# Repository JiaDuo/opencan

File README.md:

# opencan
linux系统下开源的can测试工具
基于linux驱动中slcan协议实现socketcan的通信  

## 硬件介绍  
硬件使用MicroUSB和PC主机通信，支持一路CAN 2.0B，最大波特率1Mbps
## 更新固件
使用stlink/jlink连接到J2引脚，CLK DIO GND  

linux系统下安装stlink-tools  
apt install stlink-tools  

下载固件到MCU中  
st-flash --reset write ./build/usb2can.bin 0x08000000  

## 使用
基于slcan/socketcan的软件都可以应用到当前设备，python-can、can-utils等     
* 安装can-utils  
apt install can-utils
* 建立socketcan设备  
slcand -o -s8 /dev/ttyACM0 can0   
ip link set up can0
* 收发报文
可以使用ifconfig查看can网络状态，使用can-utils中提供的软件来进行报文收发  
eg：  
candump can0  
cansniffer -c can0  
cansend can0 123#R3  

## 一些参考文档
[slcan]https://elinux.org/Bringing_CAN_interface_up  
[slcan-api]https://github.com/linux-can/can-misc/blob/master/docs/SLCAN-API.pdf

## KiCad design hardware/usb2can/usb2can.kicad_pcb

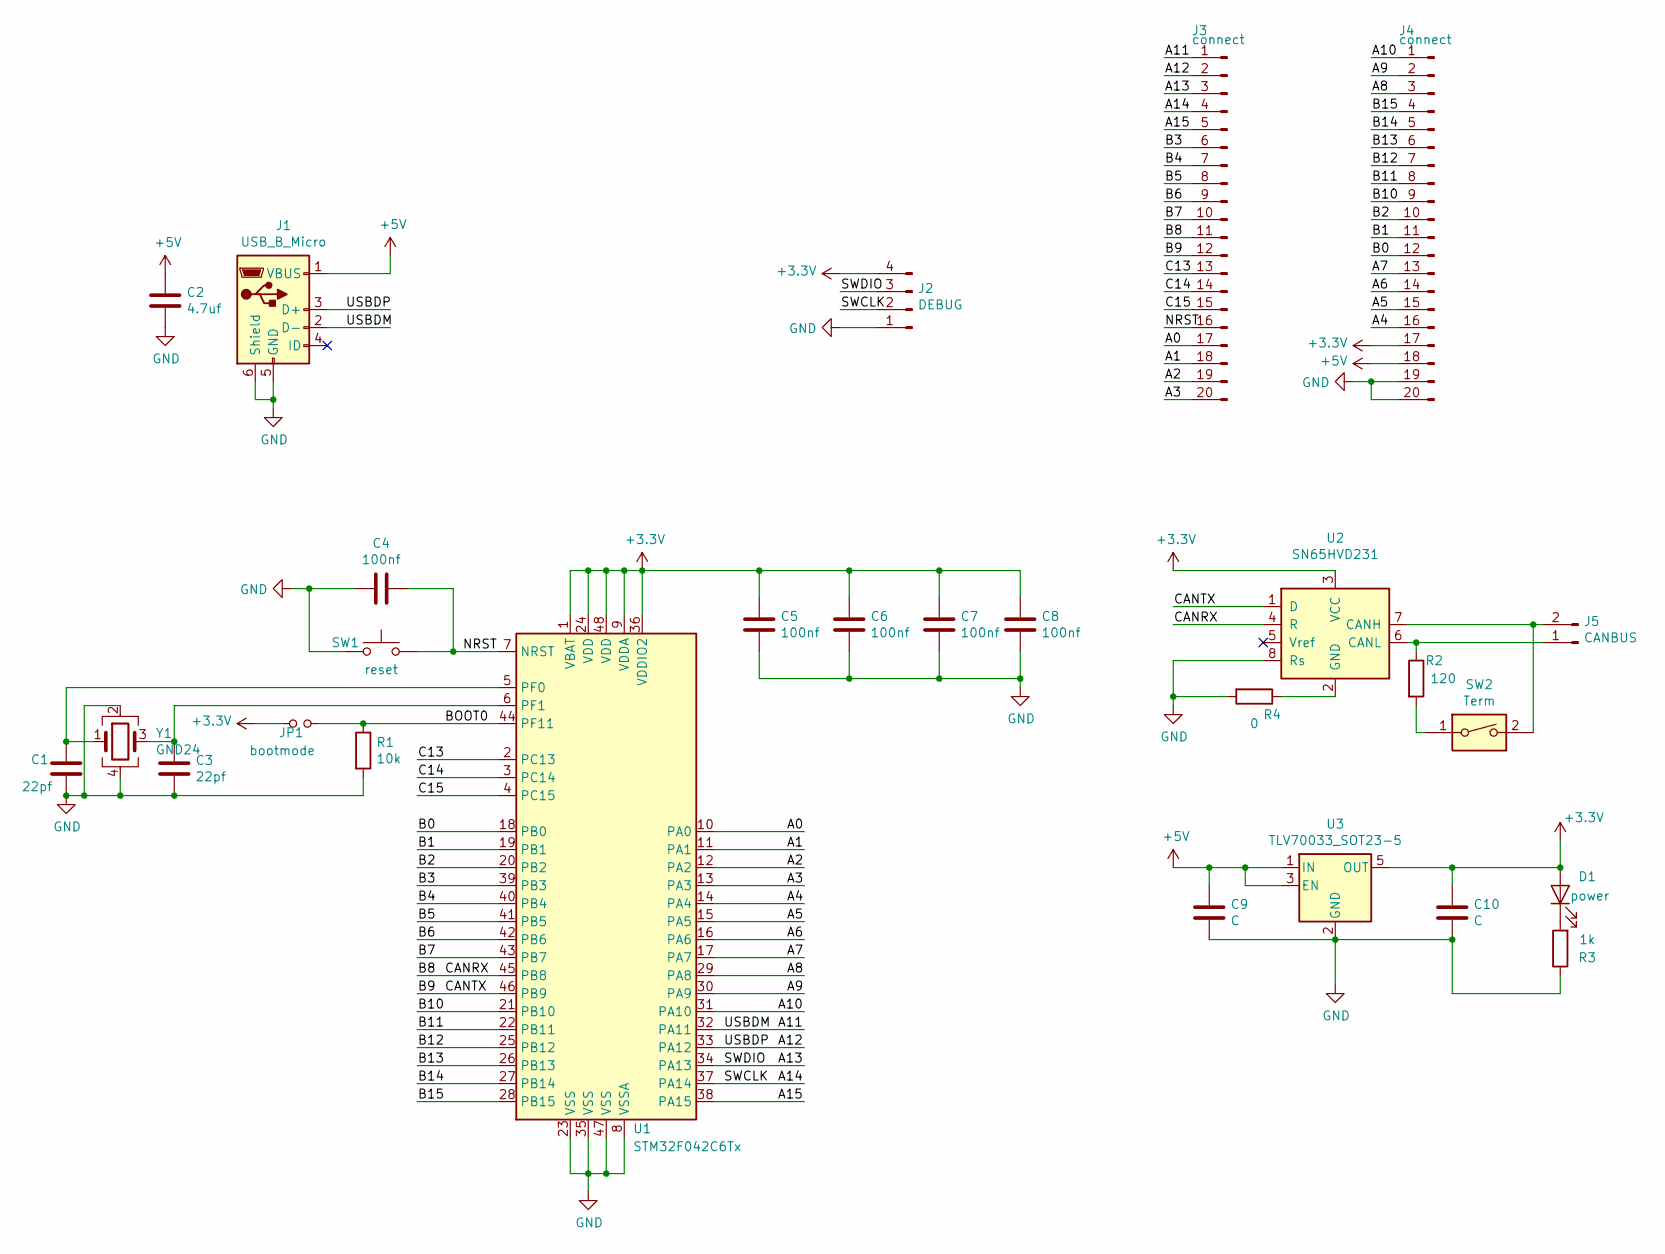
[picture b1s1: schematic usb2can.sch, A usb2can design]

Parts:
C1, C3: 22pf; C_0603_1608Metric
C2: 4.7uf; C_0805_2012Metric
C4, C5, C6, C7, C8: 100nf; C_0603_1608Metric
C9, C10: C; C_0603_1608Metric
D1: power; LED_0603_1608Metric
J1: USB_B_Micro; USB_Micro-B_Wuerth_629105150521
J2: DEBUG; PinHeader_1x04_P2.54mm_Vertical
J3, J4: connect; PinHeader_1x20_P2.54mm_Vertical
J5: CANBUS; PhoenixContact_MSTBVA_2,5_2-G_1x02_P5.00mm_Vertical
JP1: bootmode; SolderJumper-2_P1.3mm_Open_TrianglePad1.0x1.5mm
R1: 10k; R_0603_1608Metric
R2: 120; R_0603_1608Metric
R3: 1k; R_0603_1608Metric
R4: 0; R_0603_1608Metric
SW1: reset; SW_SPST_B3U-1000P
SW2: Term; SW_DIP_SPSTx01_Slide_9.78x4.72mm_W7.62mm_P2.54mm
U1: STM32F042C6Tx; LQFP-48_7x7mm_P0.5mm
U2: SN65HVD231; SOIC-8_3.9x4.9mm_P1.27mm
U3: TLV70033_SOT23-5; SOT-23-5
Y1: GND24; Crystal_SMD_3225-4Pin_3.2x2.5mm

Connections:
+3V3: C5.2, C6.2, C7.2, C8.2, C10.1, D1.2 (A), J2.4, J4.17, JP1.1, U1.1 (VBAT), U1.9 (VDDA), U1.24 (VDD), U1.36 (VDDIO2), U1.48 (VDD), U2.3 (VCC), U3.5 (OUT)
+5V: C2.1, C9.1, J1.1 (VBUS), J4.18, U3.1 (IN), U3.3 (EN)
/A0: J3.17, U1.10 (PA0)
/A1: J3.18, U1.11 (PA1)
/A2: J3.19, U1.12 (PA2)
/A3: J3.20, U1.13 (PA3)
/A4: J4.16, U1.14 (PA4)
/A5: J4.15, U1.15 (PA5)
/A6: J4.14, U1.16 (PA6)
/A7: J4.13, U1.17 (PA7)
/A8: J4.3, U1.29 (PA8)
/A9: J4.2, U1.30 (PA9)
/A10: J4.1, U1.31 (PA10)
/A11: J1.2 (D-), J3.1, U1.32 (PA11)
/A12: J1.3 (D+), J3.2, U1.33 (PA12)
/A13: J2.3, J3.3, U1.34 (PA13)
/A14: J2.2, J3.4, U1.37 (PA14)
/A15: J3.5, U1.38 (PA15)
/B0: J4.12, U1.18 (PB0)
/B1: J4.11, U1.19 (PB1)
/B2: J4.10, U1.20 (PB2)
/B3: J3.6, U1.39 (PB3)
/B4: J3.7, U1.40 (PB4)
/B5: J3.8, U1.41 (PB5)
/B6: J3.9, U1.42 (PB6)
/B7: J3.10, U1.43 (PB7)
/B8: J3.11, U1.45 (PB8), U2.4 (R)
/B9: J3.12, U1.46 (PB9), U2.1 (D)
/B10: J4.9, U1.21 (PB10)
/B11: J4.8, U1.22 (PB11)
/B12: J4.7, U1.25 (PB12)
/B13: J4.6, U1.26 (PB13)
/B14: J4.5, U1.27 (PB14)
/B15: J4.4, U1.28 (PB15)
/BOOT0: JP1.2, R1.1, U1.44 (PF11)
/C13: J3.13, U1.2 (PC13)
/C14: J3.14, U1.3 (PC14)
/C15: J3.15, U1.4 (PC15)
/NRST: C4.1, J3.16, SW1.2, U1.7 (NRST)
GND: C1.2, C2.2, C3.2, C4.2, C5.1, C6.1, C7.1, C8.1, C9.2, C10.2, J1.5 (GND), J1.6 (Shield), J2.1, J4.19, J4.20, R1.2, R3.1, R4.2, SW1.1, U1.8 (VSSA), U1.23 (VSS), U1.35 (VSS), U1.47 (VSS), U2.8 (Rs), U3.2 (GND), Y1.2, Y1.4
unnamed: C1.1, U1.5 (PF0), Y1.1
unnamed: C3.1, U1.6 (PF1), Y1.3
unnamed: D1.1 (K), R3.2
unnamed: J5.1, R2.1, U2.6 (CANL)
unnamed 45: J5.2, SW2.2, U2.7 (CANH); also elsewhere on the board
unnamed 46: R2.2, SW2.1; also elsewhere on the board
unnamed: R4.1, U2.2 (GND)

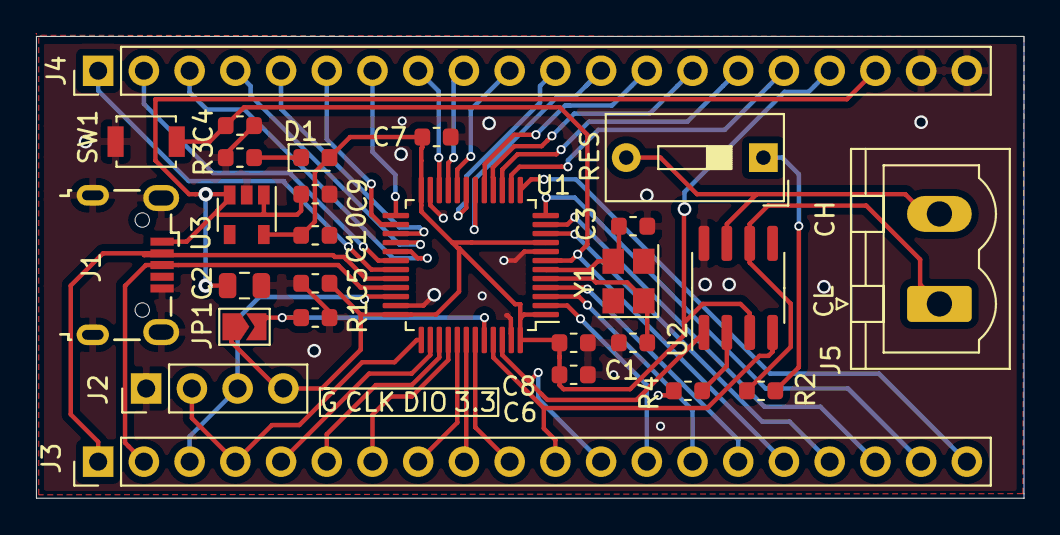
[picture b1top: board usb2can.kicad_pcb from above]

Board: 2 copper layers, 54.9 x 25.7 mm, 27 parts (0 on the bottom side), 47 nets.

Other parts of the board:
RES: Term; SW_DIP_SPSTx01_Slide_9.78x4.72mm_W7.62mm_P2.54mm

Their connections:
unnamed 45: RES.2; also elsewhere on the board
unnamed 46: RES.1; also elsewhere on the board

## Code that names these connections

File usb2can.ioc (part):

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Mcu.Name=STM32F042C(4-6)Tx
Mcu.Package=LQFP48
Mcu.UserName=STM32F042C6Tx
PA11.Mode=Device
PA11.Signal=USB_DM
PA12.Mode=Device
PA12.Signal=USB_DP
PA13.Mode=Serial_Wire
PA13.Signal=SYS_SWDIO
PA14.Mode=Serial_Wire
PA14.Signal=SYS_SWCLK
PB8.Mode=Master
PB8.Signal=CAN_RX
PB9.Mode=Master
PB9.Signal=CAN_TX
PF0-OSC_IN.Mode=HSE-External-Oscillator
PF0-OSC_IN.Signal=RCC_OSC_IN
PF1-OSC_OUT.Mode=HSE-External-Oscillator
PF1-OSC_OUT.Signal=RCC_OSC_OUT
RCC.SYSCLKFreq_VALUE=48000000
RCC.SYSCLKSource=RCC_SYSCLKSOURCE_PLLCLK
board=custom

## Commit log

2020-01-26 添加工程
2020-01-26 增加预览图片
2020-02-03 new picture
2020-02-03 update picture
2020-02-03 add picture
